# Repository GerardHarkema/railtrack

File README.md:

# Railtrack
### Modular & low-cost model RailTrack Control System 
___Note: This repository is currently under construcion. All code works, except documentation is not completed. It wil follow soon. Once the documentation is ready it will be possible to send issus about the system through this github repository.___

Welcome to this modular model railway control system. This system makes it possible to control turnout and locomotives from a graphical user panel. The system is modular and can control both classic turnouts and digitally controlled turnouts. 

## [Documentation](https://gerardharkema.github.io/railtrack/index.html)
[Licentie](licence.md)

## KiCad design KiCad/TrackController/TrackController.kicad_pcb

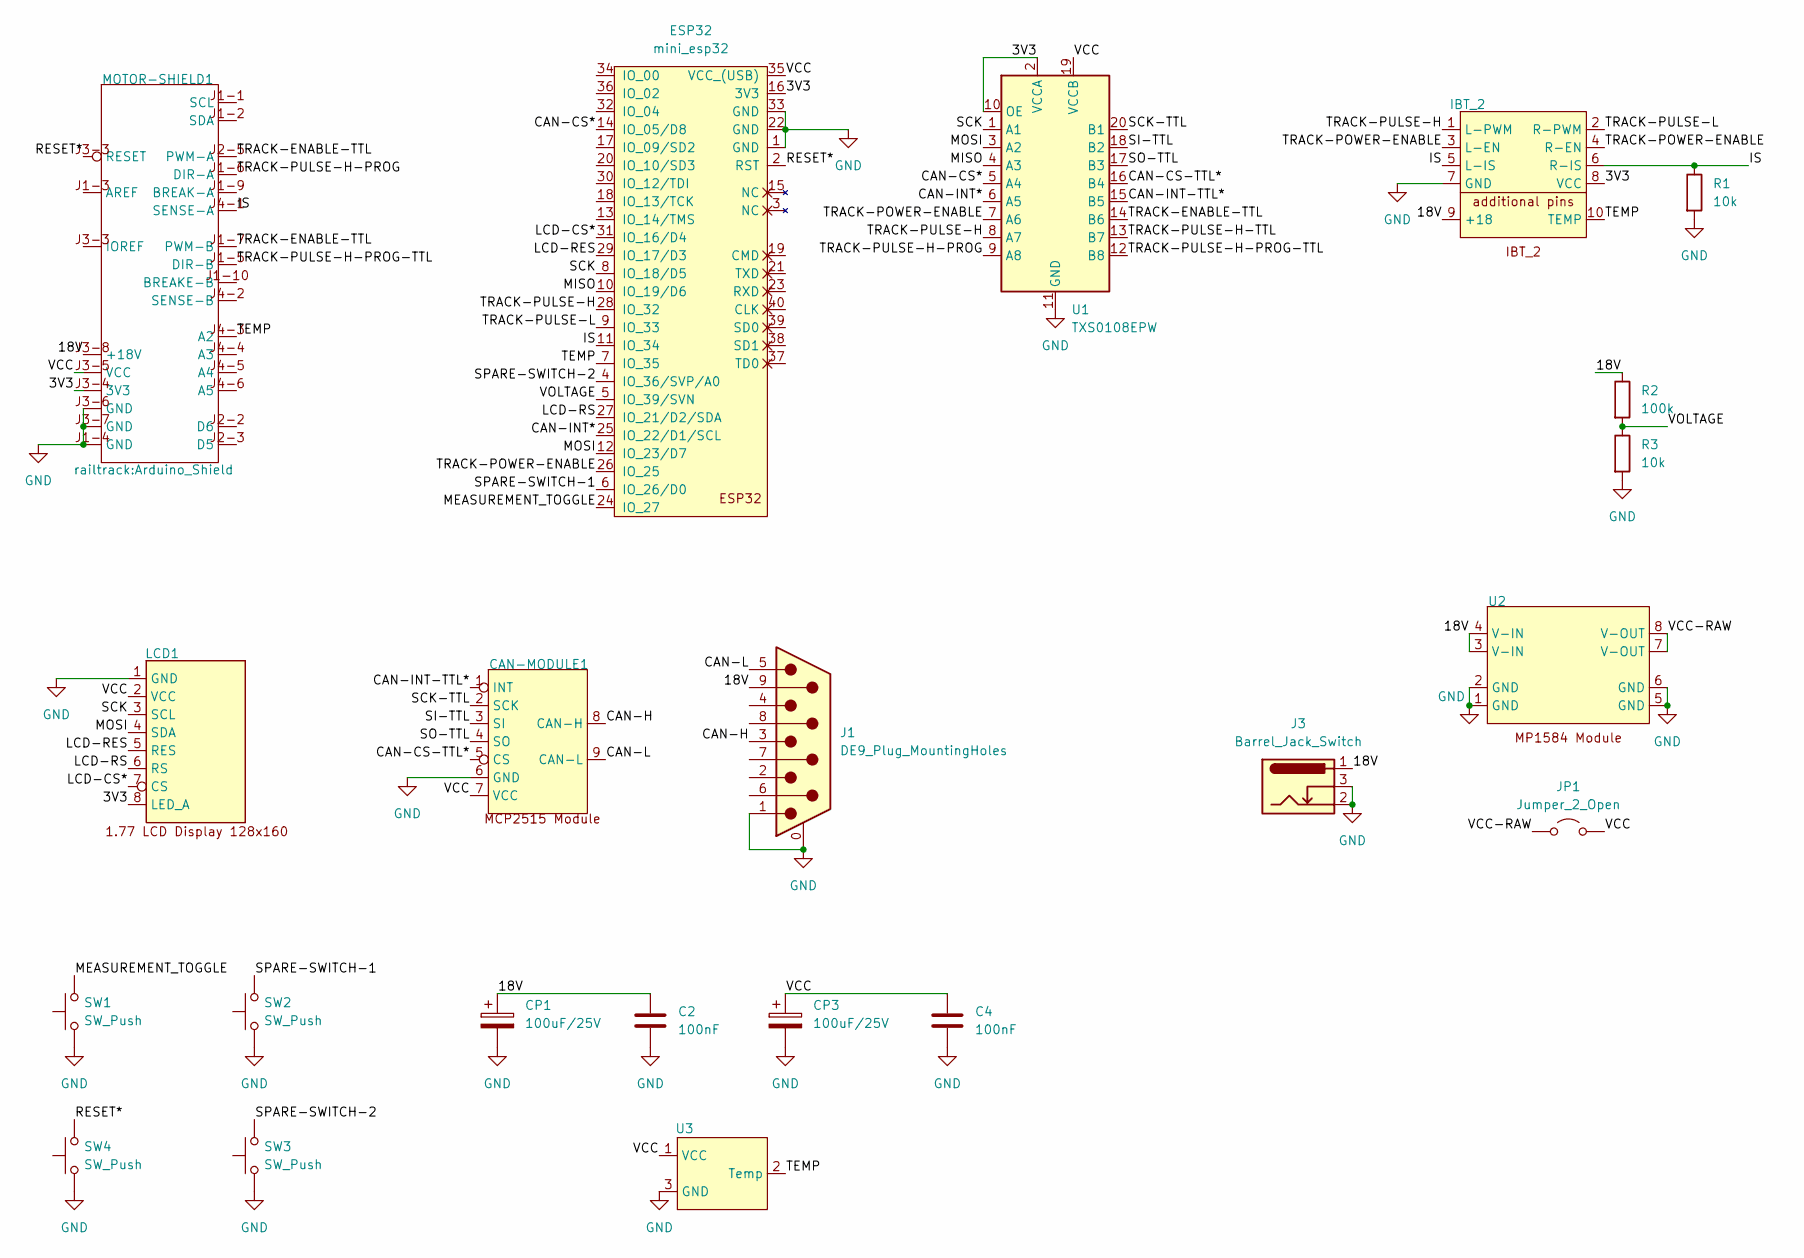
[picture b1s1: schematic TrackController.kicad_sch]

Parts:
C2, C4: 100nF; C_Disc_D5.1mm_W3.2mm_P5.00mm
CAN-MODULE1: MCP2515 Module
CP1, CP3: 100uF/25V; CP_Radial_D8.0mm_P5.00mm
ESP32: mini_esp32; ESP32_mini
IBT_2: IBT_2
J1: DE9_Plug_MountingHoles; DSUB-9_Male_Horizontal_P2.77x2.84mm_EdgePinOffset4.94mm_Hou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
J3: Barrel_Jack_Switch; BarrelJack_GCT_DCJ200-10-A_Horizontal
JP1: Jumper_2_Open; PinHeader_1x02_P2.54mm_Vertical
LCD1: 1.77 LCD Display 128x160
MOTOR-SHIELD1: Arduino_Shield
R1, R3: 10k; R_Axial_DIN0207_L6.3mm_D2.5mm_P7.62mm_Horizontal
R2: 100k; R_Axial_DIN0207_L6.3mm_D2.5mm_P7.62mm_Horizontal
SW1, SW2, SW3, SW4: SW_Push; SW_PUSH_6mm
U1: TXS0108EPW; Texas_TXS0108E_Level_Shifter_Module
U2: MP1484 Module
U3: TO-92

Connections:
/3V3: ESP32.16 (3V3), IBT_2.8 (VCC), LCD1.8 (LED_A), MOTOR-SHIELD1.J3-4 (3V3), U1.2 (VCCA), U1.10 (OE)
/18V: C2.1, CP1.1, IBT_2.9 (+18), J1.9, J3.1, MOTOR-SHIELD1.J3-8 (+18V), R2.1, U2.3 (V-IN), U2.4 (V-IN)
/CAN-CS*: ESP32.14 (IO_05/D8), U1.5 (A4)
/CAN-CS-TTL*: CAN-MODULE1.5 (CS), U1.16 (B4)
/CAN-H: CAN-MODULE1.8 (CAN-H), J1.3
/CAN-INT*: ESP32.25 (IO_22/D1/SCL), U1.6 (A5)
/CAN-INT-TTL*: CAN-MODULE1.1 (INT), U1.15 (B5)
/CAN-L: CAN-MODULE1.9 (CAN-L), J1.5
/IS: ESP32.11 (IO_34), IBT_2.5 (L-IS), IBT_2.6 (R-IS), MOTOR-SHIELD1.J4-1 (SENSE-A), R1.1
/LCD-CS*: ESP32.31 (IO_16/D4), LCD1.7 (CS)
/LCD-RES: ESP32.29 (IO_17/D3), LCD1.5 (RES)
/LCD-RS: ESP32.27 (IO_21/D2/SDA), LCD1.6 (RS)
/MEASUREMENT_TOGGLE: ESP32.24 (IO_27), SW1.2
/MISO: ESP32.10 (IO_19/D6), U1.4 (A3)
/MOSI: ESP32.12 (IO_23/D7), LCD1.4 (SDA), U1.3 (A2)
/RESET*: ESP32.2 (RST), MOTOR-SHIELD1.J3-3 (RESET), SW4.2
/SCK: ESP32.8 (IO_18/D5), LCD1.3 (SCL), U1.1 (A1)
/SCK-TTL: CAN-MODULE1.2 (SCK), U1.20 (B1)
/SI-TTL: CAN-MODULE1.3 (SI), U1.18 (B2)
/SO-TTL: CAN-MODULE1.4 (SO), U1.17 (B3)
/SPARE-SWITCH-1: ESP32.6 (IO_26/D0), SW2.2
/SPARE-SWITCH-2: ESP32.4 (IO_36/SVP/A0), SW3.2
/TEMP: ESP32.7 (IO_35), IBT_2.10 (TEMP), MOTOR-SHIELD1.J4-3 (A2), U3.2 (Temp)
/TRACK-ENABLE-TTL: MOTOR-SHIELD1.J1-7 (PWM-B), MOTOR-SHIELD1.J2-5 (PWM-A), U1.14 (B6)
/TRACK-POWER-ENABLE: ESP32.26 (IO_25), IBT_2.3 (L-EN), IBT_2.4 (R-EN), U1.7 (A6)
/TRACK-PULSE-H: ESP32.28 (IO_32), IBT_2.1 (L-PWM), U1.8 (A7)
/TRACK-PULSE-H-PROG: MOTOR-SHIELD1.J1-6 (DIR-A), U1.9 (A8)
/TRACK-PULSE-H-PROG-TTL: MOTOR-SHIELD1.J1-5 (DIR-B), U1.12 (B8)
/TRACK-PULSE-H-TTL: U1.13 (B7)
/TRACK-PULSE-L: ESP32.9 (IO_33), IBT_2.2 (R-PWM)
/VCC: C4.1, CAN-MODULE1.7 (VCC), CP3.1, ESP32.35 (VCC_(USB)), JP1.2 (B), LCD1.2 (VCC), MOTOR-SHIELD1.J3-5 (VCC), U1.19 (VCCB), U3.1 (VCC)
/VCC-RAW: JP1.1 (A), U2.7 (V-OUT), U2.8 (V-OUT)
/VOLTAGE: ESP32.5 (IO_39/SVN), R2.2, R3.1
GND: C2.2, C4.2, CAN-MODULE1.6 (GND), CP1.2, CP3.2, ESP32.1 (GND), ESP32.22 (GND), ESP32.33 (GND), IBT_2.7 (GND), J1.0 (PAD), J1.1, J3.2, J3.3, LCD1.1 (GND), MOTOR-SHIELD1.J1-4 (GND), MOTOR-SHIELD1.J3-6 (GND), MOTOR-SHIELD1.J3-7 (GND), R1.2, R3.2, SW1.1, SW2.1, SW3.1, SW4.1, U1.11 (GND), U2.1 (GND), U2.2 (GND), U2.5 (GND), U2.6 (GND), U3.3 (GND)

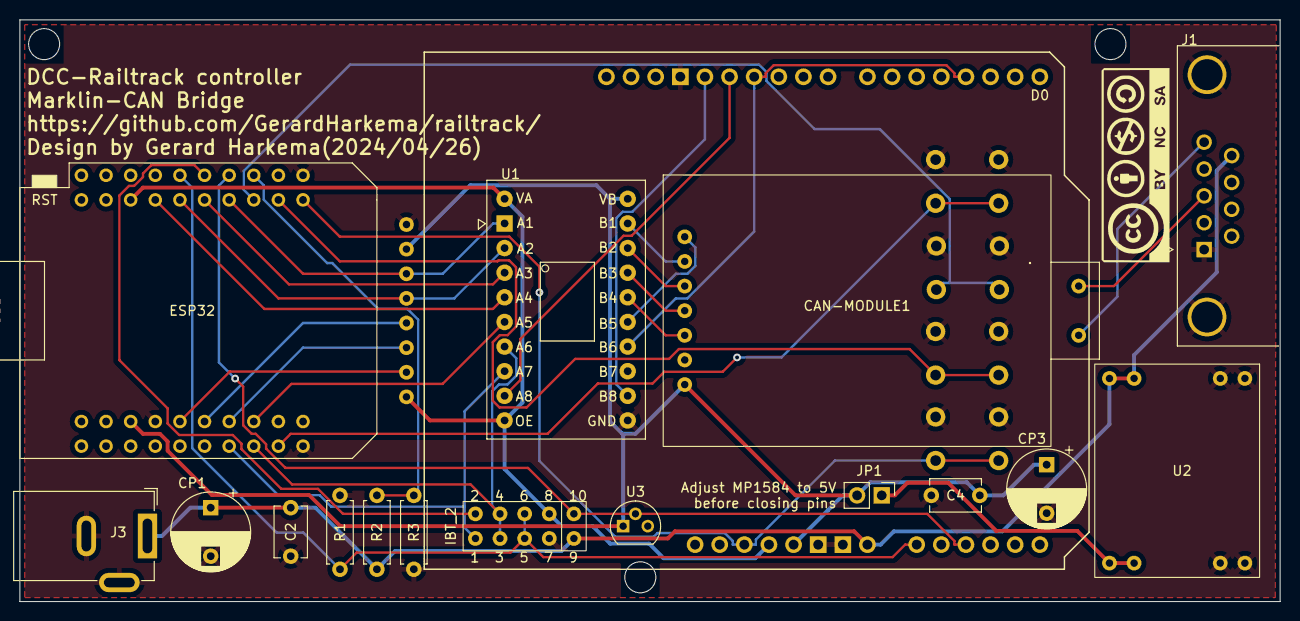
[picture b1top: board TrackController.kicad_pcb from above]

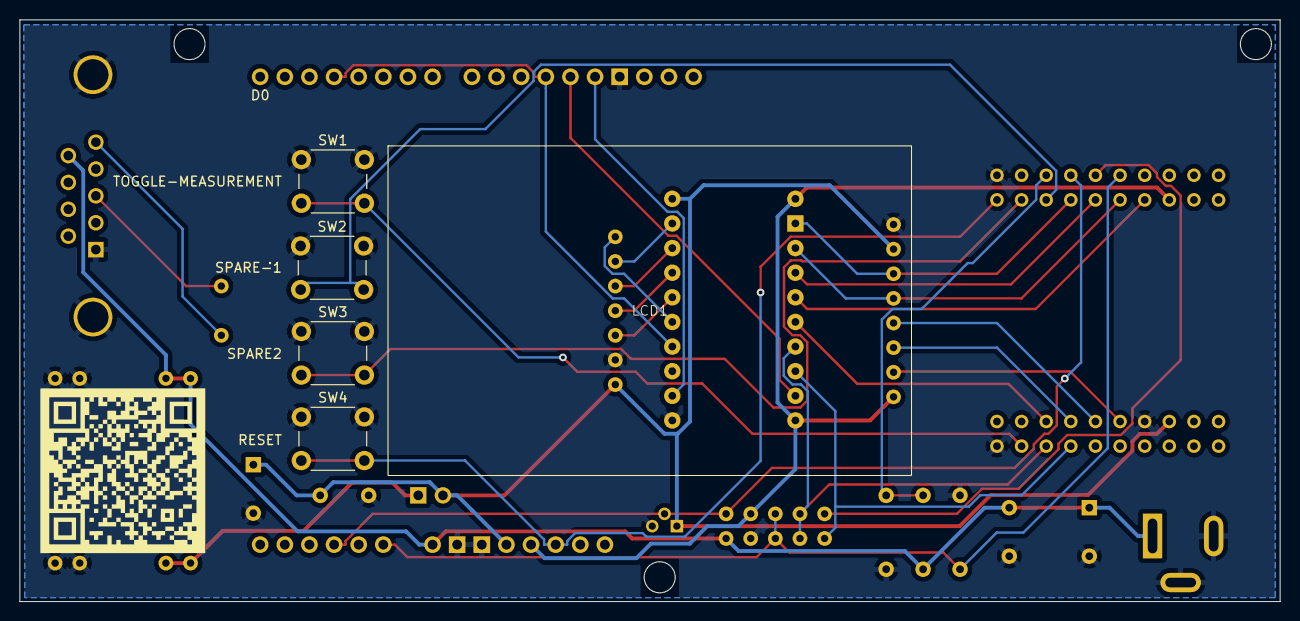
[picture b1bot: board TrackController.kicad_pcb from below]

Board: 2 copper layers, 130.0 x 60.0 mm, 23 parts (5 on the bottom side), 33 nets.

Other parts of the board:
G1: LOGO

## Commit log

2024-02-25 20240225
2024-02-26 20240226
2024-02-27 20240227
2024-02-29 20240229
2024-03-01 20240301
2024-03-03 20240303
2024-03-04 20240304
2024-03-05 20240405
2024-03-08 20240408
2024-03-10 20240410
2024-03-14 20240414
2024-03-15 20240415
2024-03-16 20240416
2024-03-22 Some small bug-fixes
2024-03-23 Documentation Update Added hostnames for Wifi
2024-03-23 Documentation update
2024-03-27 Started DCC Controller implementation
2024-03-27 Added timer support for ESP32 in DCC controller
2024-03-29 added dcc protocol test
2024-03-31 DCC protocol thread save
2024-04-01 Protocol description changed in config
2024-04-01 Added current measurements
2024-04-02 Added voltage and temperature monitoring
2024-04-03 20240403
2024-04-05 Implementation Interrupts DCC MM controller
2024-04-07 20240407
2024-04-09 20240409
2024-04-09 added DCC-Ex
2024-04-17 20240417
2024-04-18 Added maintenance support en decoposition
2024-04-19 20240419
2024-04-19 20240419 Project update & bug fixes dcc mm
2024-04-19 20240419-1
2024-04-19 Start of implementing maintenace mode
2024-04-20 Added KiCAD pcb design
2024-04-22 20240422
2024-04-23 20240423
2024-04-26 20240425
2024-04-29 Added Schematics and PCB desgn(pdf)
2024-05-07 20240507
2024-05-08 20240508
2024-05-14 20240514
2024-10-02 241002
2024-10-06 20241006
2024-10-06 Test Credentials
2024-10-08 241008
2024-10-10 241010
2024-10-13 241013
2024-10-25 20241025
2024-10-27 20241027
2024-10-28 20241018
2024-10-29 20241029
2024-10-29 20241029-1
2024-10-30 20241030
2025-01-02 20250102
2025-01-03 20250103
2025-01-03 20250103-2
2025-01-04 20250104
2025-01-04 20250114-documetation added
2025-01-04 20250104-documentation update
2025-01-05 20250105
2025-01-06 20250116
2025-01-07 20240106
2025-01-07 deploy: 1ea8b6e7ebd2e3318700d0013ce5c80951e6a5f6
2025-01-08 20250107
2025-01-09 20250109
2025-01-11 20250111
2025-01-14 20250114
2025-01-15 20250115
2025-01-17 20250117
2025-01-18 20250118
2025-01-19 20250119
2025-01-24 20150124
2025-01-27 20250127
2025-01-29 20250129
2025-01-30 20250130
2025-02-13 20250213
2025-02-16 20250216
2025-02-18 20250218
2025-02-20 20250220
2025-02-20 deploy: 47373c518df43b963564949d3f2526e22c1f7b7f
2025-02-23 20250223
2025-02-24 20250224
2025-02-24 deploy: c52a0160b5fd9a7ba74c174d8549eff196af1996
2025-03-12 20250312
2025-03-25 20250325
2025-03-25 deploy: 3c252f12ddf7cc94660a853bc61ae1bfadfbcd28
2025-03-30 transfeur to Jazzy
2025-10-22 20251022
2025-11-02 20251102
2025-11-04 20251104
2025-11-21 20251121
2025-12-09 20251209
2025-12-11 added ESP restart after fatal error
2025-12-23 20251223
2026-01-01 20260101
2026-01-01 deploy: 0f2c11b6cb4aba71180e3e314b329270cdbc48e7
